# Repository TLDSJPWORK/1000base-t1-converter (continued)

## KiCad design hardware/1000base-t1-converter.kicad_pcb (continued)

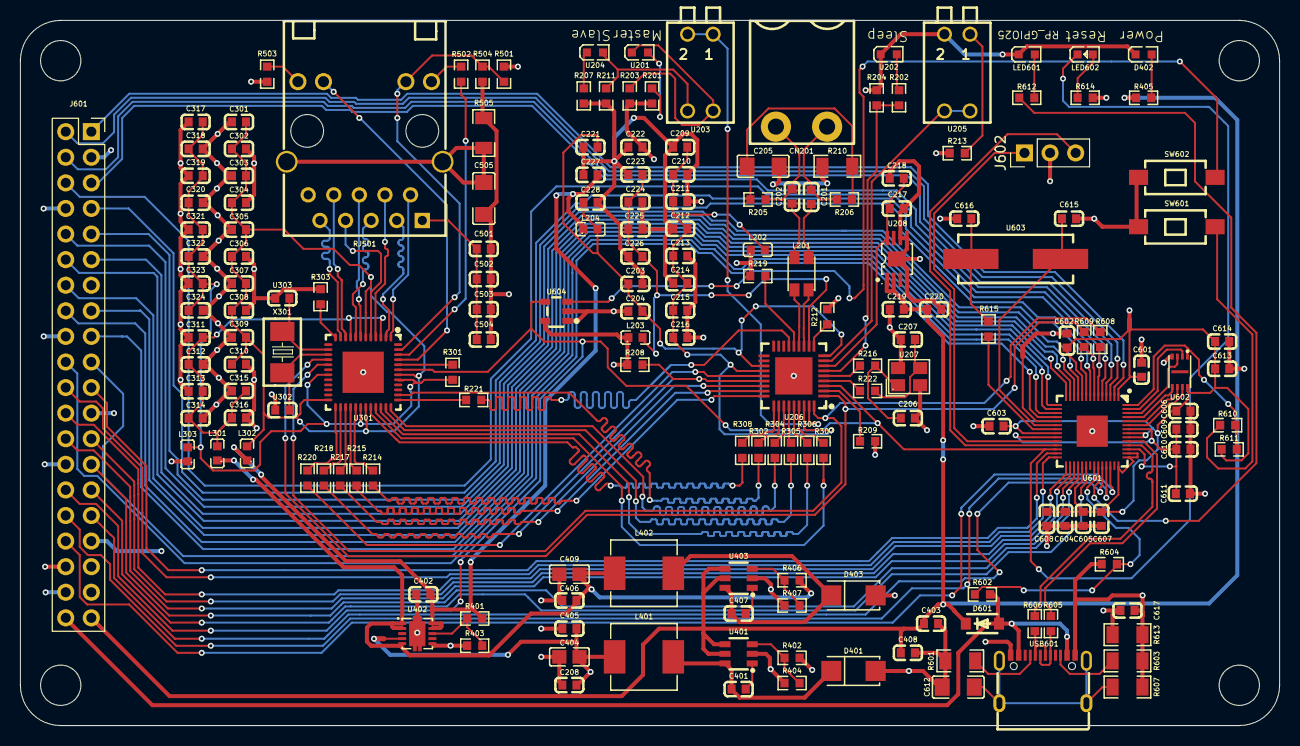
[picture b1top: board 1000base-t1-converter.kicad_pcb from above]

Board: 4 copper layers, 125.0 x 70.0 mm, 184 parts (0 on the bottom side), 144 nets.

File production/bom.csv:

Designator,Footprint,Quantity,Value,LCSC Part #
"C201, C202, C203, C204, C211, C213, C215, C216, C217, C220, C221, C225, C304, C306, C308, C310, C314, C316, C320, C322, C324, C401, C407, C501, C502, C503, C504, C601, C602, C603, C604, C605, C606, C607, C609, C610, C614, C617",C0603,38,0.1uF,C14663
C205,C1206,1,1kV 4700pF,C9192
"C206, C207",C0603,2,50V 22pF,C326840
"C208, C209, C218, C222, C223, C227, C228, C301, C311, C317",C0603,10,10V 10uF,C237435
"C210, C224, C302, C312, C318, C405, C406, C608, C611",C0603,9,1uF, C15849
"C212, C214, C226, C303, C305, C307, C309, C313, C315, C319, C321, C323",C0603,12,50V 0.01uF,C57112
"C219, C402",C0603,2,25V 10uF,C96446
"C403, C408, C613",C0603,3,2.2uF,C307463
"C404, C409",C0805,2,47uF,C124129
"C505, C612",C1206,2,1kV 0.01uF,C107192
"C615, C616",C0603,2,27pF,C107045
CN201,CONN-TH_WJ2EDGR-5.08-2P,1,WJ2EDGR-5.08-2P,C8383
"D401, D403",SMA_L4.3-W2.6-LS5.2-RD,2,B160-13-F,C24784
"D402, U201, U202, U204",LED0603-RD_GREEN,4,PSC-1608U52GC-G4,C22371297
D601,SOD-123F_L2.8-W1.8-LS3.7-RD,1,MBR120VLSFT1G,C223608
J601,PinSocket_2x20_P2.54mm_Vertical,1,Conn_02x20_Counter_Clockwise,
J602,PinHeader_1x03_P2.54mm_Vertical,1,Conn_01x03_Pin,
L201,FILTER-SMD_4P-L3.2-W2.5-BL_DLW32SH510XK2L,1,DLW32MH201XK2L,C883600
"L202, L203, L204, L301, L302, L303",L0603,6,BLM18KG102BH1D,C560058
"L401, L402",IND-SMD_L7.1-W6.6,2,15uH,C149585
LED601,LED0603-RD_GREEN,1,TJ-S1608CY6T5ALC7K-A5,C440520
LED602,LED0603-RD_RED,1,XL-1608SURC-06,C965799
"R201, R202, R207, R209, R212, R213, R301, R614",R0603,8,2.2k,C4190
"R203, R204, R208, R211, R504",R0603,5,2.49k,C22908
"R205, R206",R0603,2,1.0k 0.25W,C2653986
"R210, R505, R607, R613",R1206,4,1M 0.25W,C108083
"R214, R215, R217, R218, R220, R221, R302, R304, R305, R306, R307, R308, R608, R609",R0603,14,22,C108405
R216,R0603,1,100,C22775
"R219, R604",R0603,2,10.0k,C25804
"R222, R610, R615",R0603,3,1k, C21190
R303,R0603,1,11k,C137801
R401,R0603,1,1.30k,C705951
R402,R0603,1,3.40k,C705984
R403,R0603,1,4.42k,C728617
"R404, R407",R0603,2,1.02k,C705819
R405,R0603,1,22k,C31850
R406,R0603,1,2.26k,C861811
R501,R0603,1,5.76k,C23070
"R502, R503, R612",R0603,3,470,C23179
"R601, R603",R1206,2,5.1k,C163372
R602,R0603,1,5.6k,C23189
"R605, R606",R0603,2,27,C137753
R611,R0603,1,DNF,
RJ501,RJ45-TH_HR911130A,1,HR911130A,C54408
"SW601, SW602",SW-SMD_L6.0-W3.3-LS8.0,2,TS-1101-C-W,C318938
"U203, U205",SW-TH_4P-P2.54_SMQP-02R-TP,2,SMQP-02R-TP,C5299482
U206,UQFN-36_L6.0-W6.0-P0.50-BL-EP3.7,1,DP83TG720RWRHATQ1,C2921292
U207,CRYSTAL-SMD_4P-L3.2-W2.5-BL,1,ABM8AIG-25.000MHZ-12-2Z-T3,C1985412
U208,HVSSOP-8_L3.0-W3.0-P0.65-LS4.9-BL-EP,1,TPS7B8233QDGNRQ1,C5220182
U301,VQFN-48_L7.0-W7.0-P0.50-BL-EP4.1,1,DP83867ERGZR,C913839
"U302, U303",C0603,2,25V 27pF,C1656
"U401, U403",SOT-23-6_L2.9-W1.6-P0.95-LS2.8-BR,2,LMR14206XMKX/NOPB,C48239
U402,VSON-10_L3.0-W3.0-P0.50-TL-EP,1,TPS74701DRCR,C105262
U601,LQFN-56_L7.0-W7.0-P0.4-EP,1,RP2040,C2040
U602,USON-8_L3.0-W2.0-P0.50-BL-EP,1,W25Q16JVUXIQ,C2843335
U603,CRYSTAL-SMD_L11.5-W4.8-LS12.7,1,ABLS-12.000MHZ-B4-T,C596818
U604,SOT-23-5_L2.9-W1.6-P0.95-LS2.8-BR,1,TPS3838K33QDBVRQ1,C702198
USB601,USB-C-SMD_TYPE-C-6PIN-2MD-073,1,TYPE-C 16PIN 2MD(073),C2765186
X301,OSC-SMD_L5.0-W3.2,1,NX5032GA-25.000M-STD-CSK-4,C115092
